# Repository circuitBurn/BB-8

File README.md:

# PCB files and Arduino sketches for FrSky SBUS control of Joe's Drive

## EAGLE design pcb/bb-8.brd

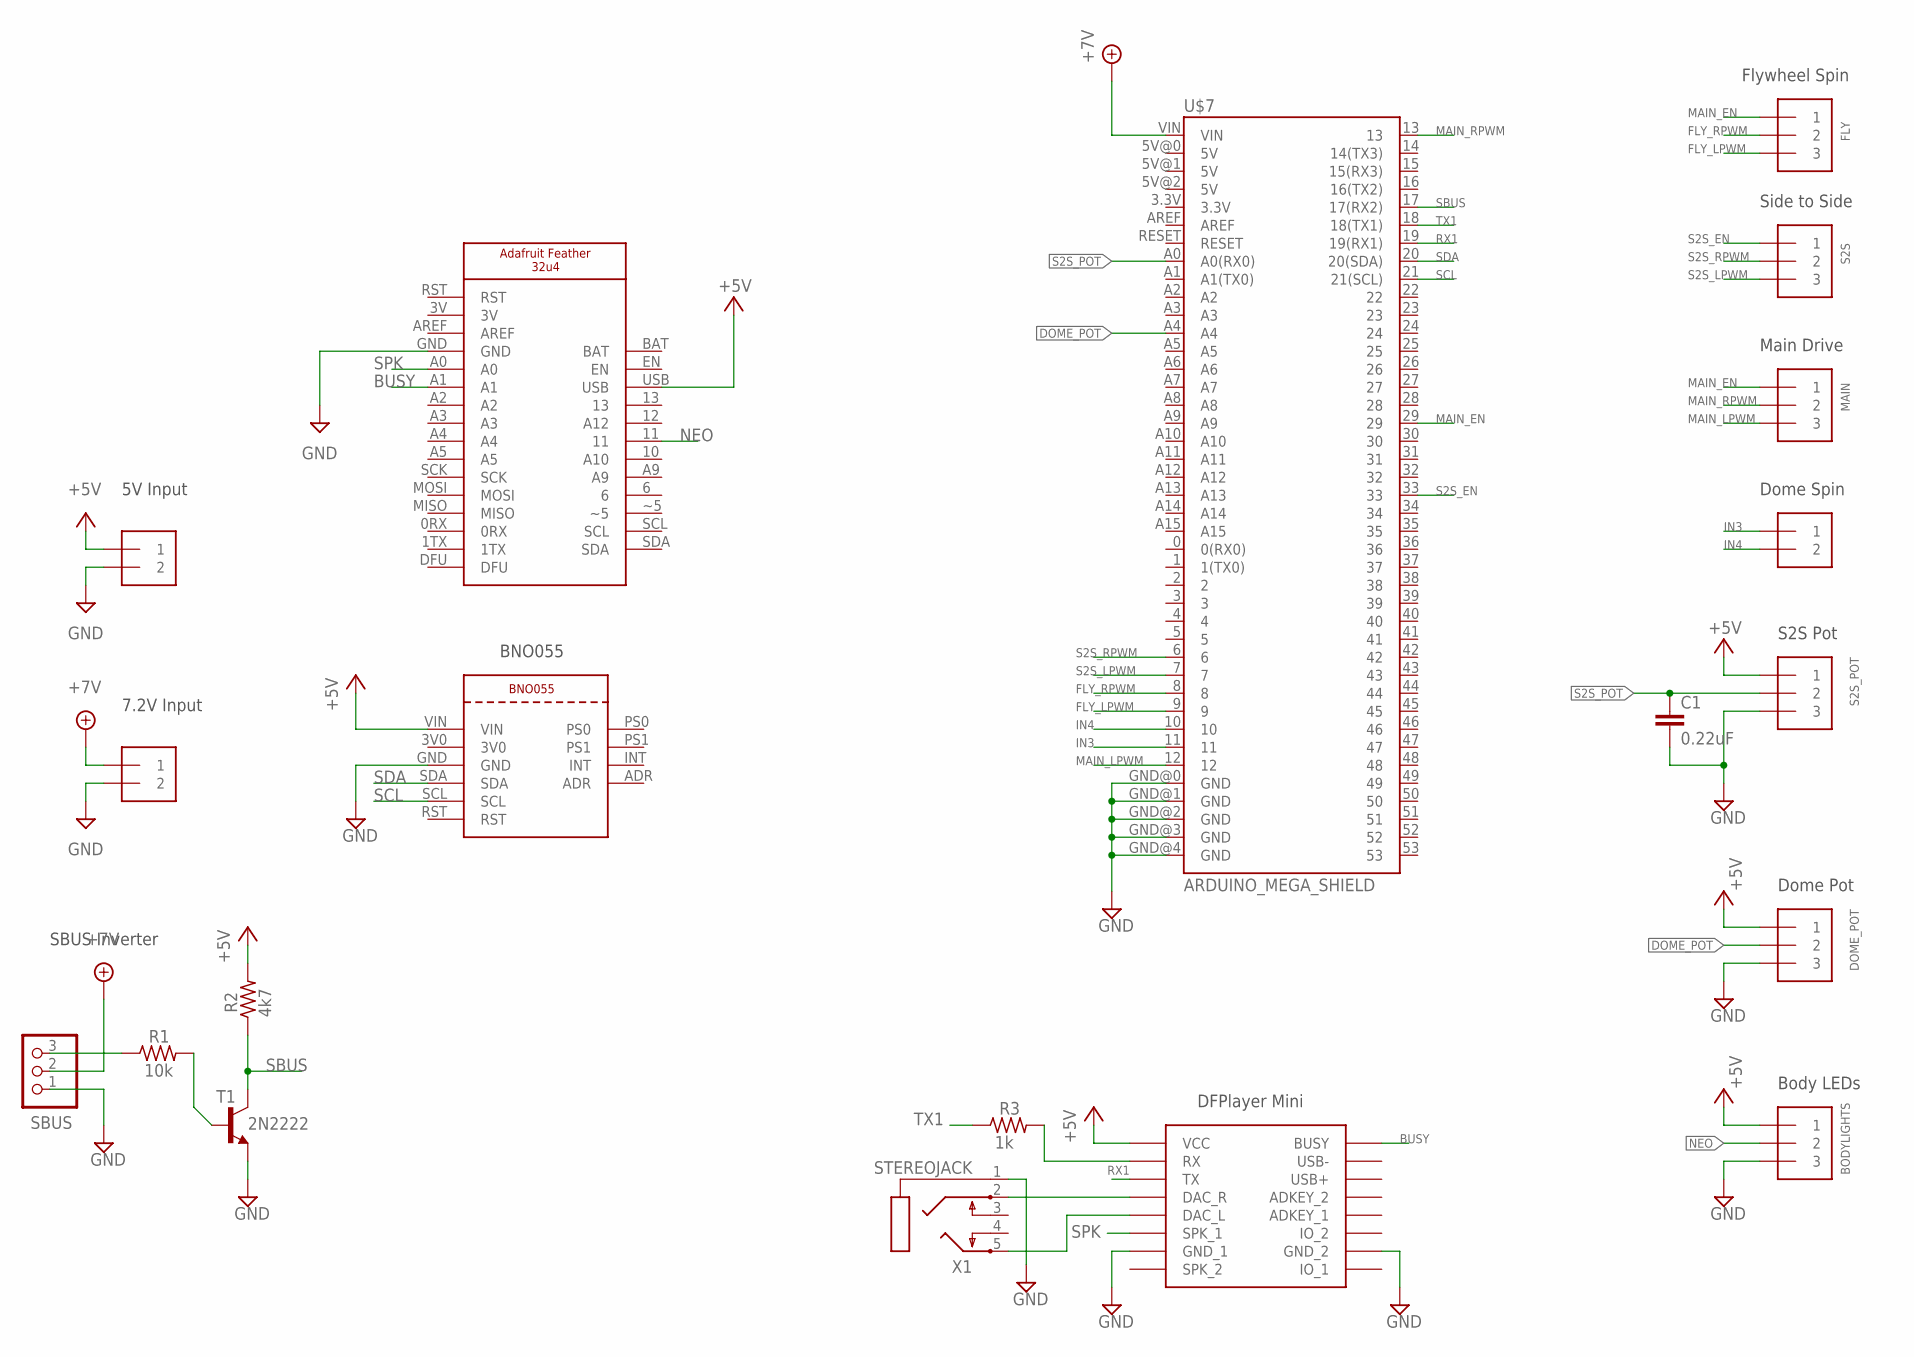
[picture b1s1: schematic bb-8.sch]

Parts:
5V, 7V2: 1X2-3.5MM
BODYLIGHTS: SCREW_TERMINAL_3_PIN
C1: 0.22uF; C050-024X044
DOME: 1X2-3.5MM
DOME_POT: SCREW_TERMINAL_3_PIN
FLY: SCREW_TERMINAL_3_PIN
MAIN: SCREW_TERMINAL_3_PIN
R1: 10k; 0204/7
R2: 4k7; 0204/7
R3: 1k; 0204/7
S2S, S2S_POT: SCREW_TERMINAL_3_PIN
SBUS: PINHD-1X3; 1X03
T1: 2N2222; TO92-EBC-OVAL
U$1: DFPLAYER
U$2: ADAFRUIT_BNO055
U$3: ADAFRUIT_FEATHER_32U4
U$7: ARDUINO_MEGA_SHIELD
X1: STEREOJACK; STX3100

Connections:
+5V: 5V.1, BODYLIGHTS.1, DOME_POT.1, R2.2, S2S_POT.1, U$1.VCC, U$2.VIN, U$3.USB
+7V: 7V2.1, SBUS.2, U$7.VIN
BUSY: U$1.BUSY, U$3.A1
DAC_R: U$1.DAC_R, X1.2
DOME_POT: DOME_POT.2, U$7.A4
FLY_LPWM: FLY.3, U$7.9
FLY_RPWM: FLY.2, U$7.8
GND: 5V.2, 7V2.2, BODYLIGHTS.3, C1.2, DOME_POT.3, S2S_POT.3, SBUS.1, T1.E, U$1.GND_1, U$1.GND_2, U$2.GND, U$3.GND, U$7.GND@0 (GND), U$7.GND@1 (GND), U$7.GND@2 (GND), U$7.GND@3 (GND), U$7.GND@4 (GND), X1.1
IN3: DOME.1, U$7.11
IN4: DOME.2, U$7.10
MAIN_EN: FLY.1, MAIN.1, U$7.29
MAIN_LPWM: MAIN.3, U$7.12
MAIN_RPWM: MAIN.2, U$7.13
unnamed: R1.2, T1.B
unnamed: R3.2, U$1.RX
unnamed: R1.1, SBUS.3
unnamed: U$1.DAC_L, X1.5
NEO: BODYLIGHTS.2, U$3.11
RX1: U$1.TX, U$7.19 (19(RX1))
S2S_EN: S2S.1, U$7.33
S2S_LPWM: S2S.3, U$7.7
S2S_POT: C1.1, S2S_POT.2, U$7.A0 (A0(RX0))
S2S_RPWM: S2S.2, U$7.6
SBUS: R2.1, T1.C, U$7.17 (17(RX2))
SCL: U$2.SCL, U$7.21 (21(SCL))
SDA: U$2.SDA, U$7.20 (20(SDA))
SPK: U$1.SPK1 (SPK_1), U$3.A0
TX1: R3.1, U$7.18 (18(TX1))

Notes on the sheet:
5V Input
7.2V Input
DFPlayer Mini
S2S Pot
Dome Pot
Flywheel Spin
Side to Side
Main Drive
Dome Spin
SBUS Inverter
BNO055
Body LEDs

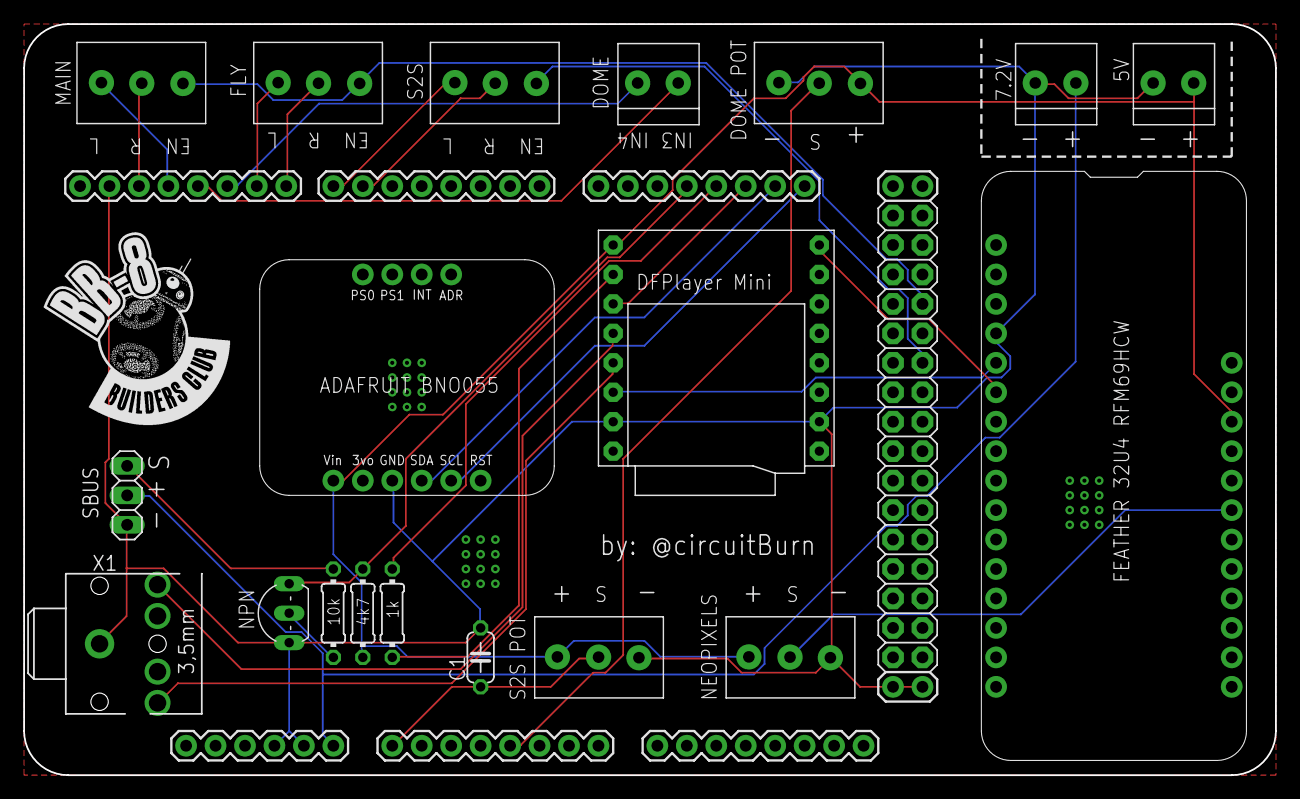
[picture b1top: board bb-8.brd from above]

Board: 2 copper layers, 108.0 x 64.8 mm, 20 parts (0 on the bottom side), 28 nets.

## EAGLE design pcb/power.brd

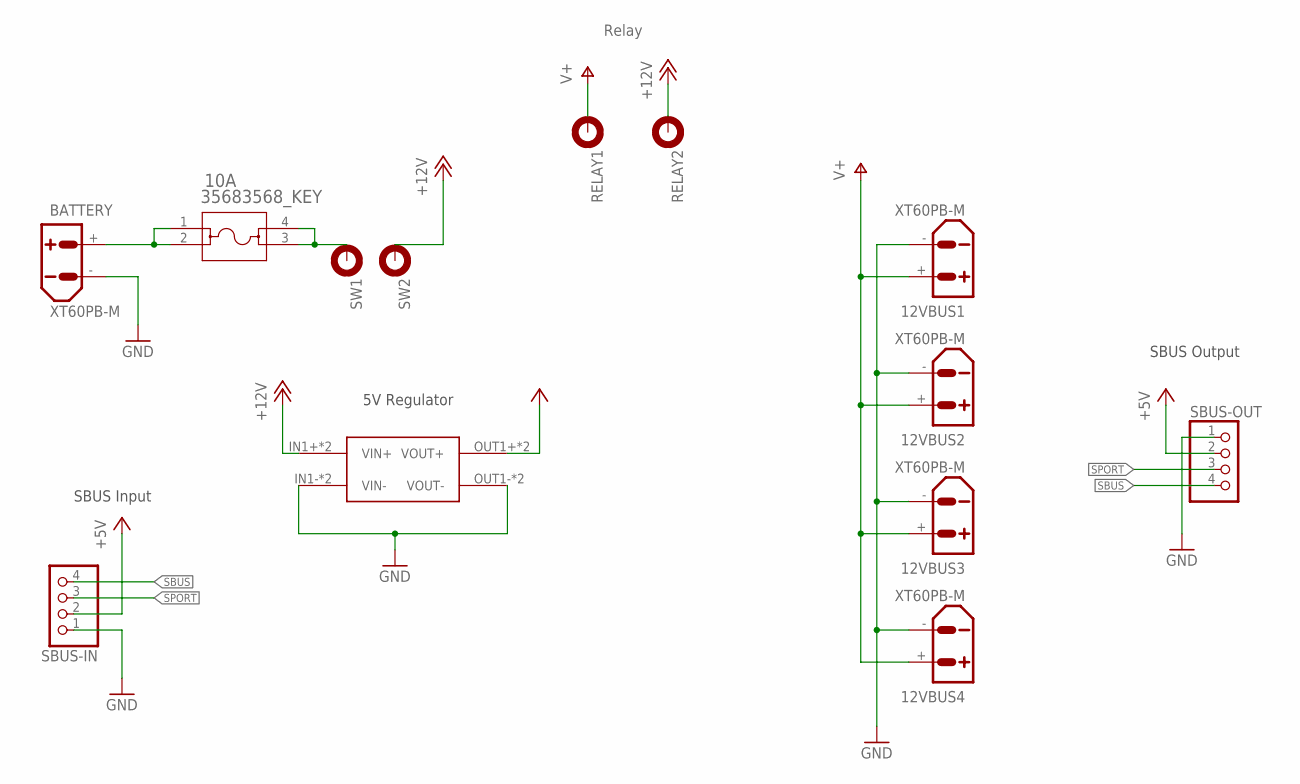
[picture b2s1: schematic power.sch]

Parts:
10A: 35683568_KEY; 3568_KEY
12VBUS1, 12VBUS2, 12VBUS3, 12VBUS4: XT60PB-M
BATTERY: XT60PB-M
RELAY1, RELAY2: MOUNT-PAD-ROUND2.8; 2,8-PAD
SBUS-IN: PINHD-1X4; 1X04
SBUS-OUT: PINHD-1X4; 1X04
SW1, SW2: MOUNT-PAD-ROUND2.8; 2,8-PAD
U$2: MP1584; DC-BRICK

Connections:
+5V: SBUS-IN.2, SBUS-OUT.2, U$2.OUT1+ (VOUT+), U$2.OUT2+ (VOUT+)
+12V: RELAY2.B2,8, SW2.B2,8, U$2.IN1+ (VIN+), U$2.IN2+ (VIN+)
GND: 12VBUS1.-, 12VBUS2.-, 12VBUS3.-, 12VBUS4.-, BATTERY.-, SBUS-IN.1, SBUS-OUT.1, U$2.IN1- (VIN-), U$2.IN2- (VIN-), U$2.OUT1- (VOUT-), U$2.OUT2- (VOUT-)
unnamed: 10A.1, 10A.2, BATTERY.+
unnamed: 10A.3, 10A.4, SW1.B2,8
SBUS: SBUS-IN.4, SBUS-OUT.4
SPORT: SBUS-IN.3, SBUS-OUT.3
V+: 12VBUS1.+, 12VBUS2.+, 12VBUS3.+, 12VBUS4.+, RELAY1.B2,8

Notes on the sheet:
SBUS Output
5V Regulator
SBUS Input
Relay

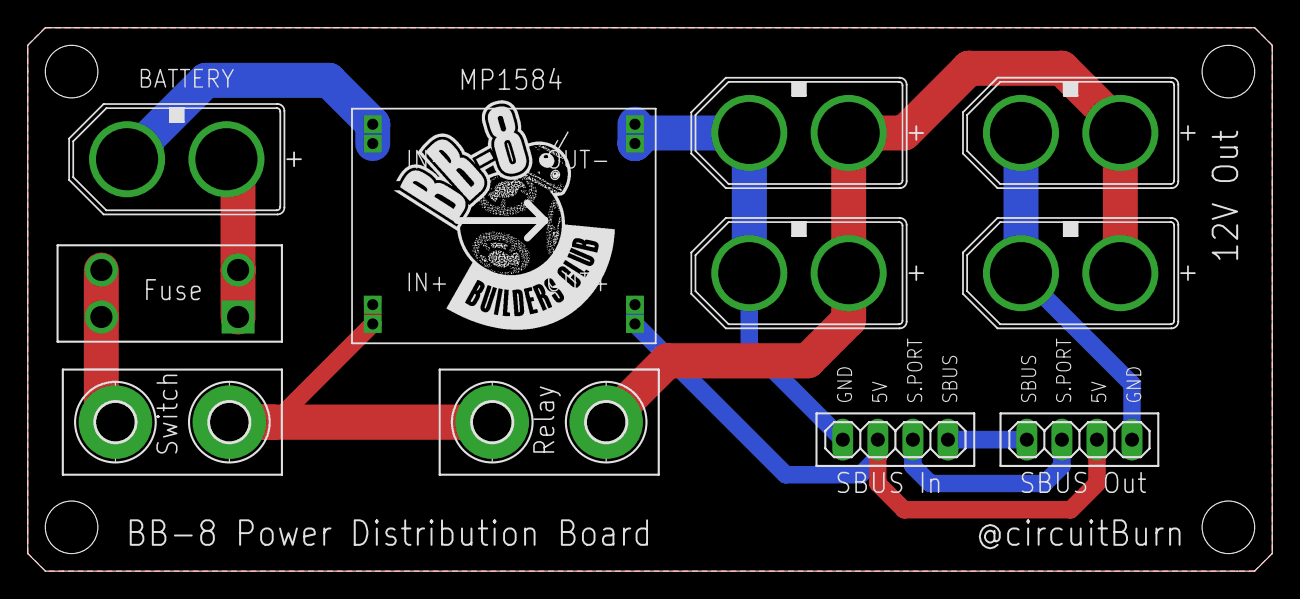
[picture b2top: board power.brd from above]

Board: 2 copper layers, 90.2 x 39.4 mm, 13 parts (0 on the bottom side), 8 nets.

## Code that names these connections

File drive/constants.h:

/*****************************************************************************/
// RC Values
// - These are defined by the limits of your transmitter
/*****************************************************************************/
#define RC_MIN 172
#define RC_MID 992
#define RC_MAX 1811

/*****************************************************************************/
// RC Deadband
// - Set a range of values to be considered "off"
// - Anything in between these values is "off"
/*****************************************************************************/
#define RC_DEADBAND_LOW 962
#define RC_DEADBAND_HIGH 978

/*****************************************************************************/
// RC Channel Mapping
// - The channels are N - 1 where N is the defined channel number on the transmitter
// - Ex: CH1 on Tx is 0 here, CH2 is 1
/*****************************************************************************/
#define CH_DRIVE_MAIN 0
// 1: Channel 2 is directly connected to dome servo
// 2: Channel 3 is directly connected to dome servo 
#define CH_DRIVE_S2S 3
#define CH_FLYWHEEL 4
#define CH_DOME_SPIN 5
// 6: Channel 7 is the RC relay
#define CH_SOUND_TRIGGER 7
#define CH_SOUND_BANK 8
#define CH_DRIVE_EN 9
#define CH_DIRECTION 10
#define CH_ROLL_OFFSET 11
#define CH_FLYWHEEL_EN 12
#define CH_S2S_OFFSET 13
#define CH_RANDOM_SOUND 14

/*****************************************************************************/
// Main drive motor controller
/*****************************************************************************/
#define DRIVE_R_PWM_PIN 13
#define DRIVE_L_PWM_PIN 12
#define DRIVE_EN_PIN 29
#define MAX_DRIVE_SPEED 125 // 0 - 255

/*****************************************************************************/
// Flywheel motor controller
/*****************************************************************************/
#define FLYWHEEL_R_PWM_PIN 8
#define FLYWHEEL_L_PWM_PIN 9

/*****************************************************************************/
// Side to side motor controller
/*****************************************************************************/
#define S2S_R_PWM_PIN 6
#define S2S_L_PWM_PIN 7
#define S2S_EN_PIN 33
#define S2S_POT_PIN A0
#define S2S_MAX_ANGLE 40
#define S2S_EASING 0.9
#define S2S_OFFSET 0 // Negative value here will tilt the drive to the right

/*****************************************************************************/
// Dome servos and spin motor
/*****************************************************************************/
#define DOME_SPIN_A_PIN 10
#define DOME_SPIN_B_PIN 11
#define DOME_POT_PIN A4
#define DOME_SPIN_SPEED 125 // 0 - 255 for spinning completely around
#define DOME_TURN_SPEED 100 // 0 - 255 for looking around
#define DOME_POT_OFFSET 20

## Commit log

2021-07-19 Adding EAGLE PCB schematic and board files
2021-07-31 Initial commit of existing code
2021-09-07 S2S working
2021-09-08 Adding drive feather sketch
2021-09-21 Body Neopixels
2021-09-21 S2S and audio update
2021-09-27 PSI synch
2021-10-07 Big updates
2021-10-13 Fixing dome servo code
2021-10-20 Side to side enhancements
2021-10-20 Update Feather encryption keys
2021-11-05 Moving to 3 axis stick for dome rotation
2021-11-14 Add bodge factor to S2S
2021-12-21 Schematic updates
2022-03-21 A few updates
2022-07-01 Splitting up drive functions into separate files
2022-08-20 Squashed commit of the following:
    commit c327650e5103bb6a6949c6a1538a163dea4dba5a
    Author: Patrick Ryan <pat.m.ryan@gmail.com>
    Date: Sat Aug 20 09:49:49 2022 -0400
    Updates to PCB
    commit 971e034c2edcb3dc5db781baa092387508605f21
    Author: Patrick Ryan <pat.m.ryan@gmail.com>
2022-11-03 Adding quick reverse switch
2023-03-15 Updating sbus library and speed settings
2023-06-17 s2s updates
2023-09-07 Better stabilization
2023-11-05 Updates for horus conversion
2023-11-05 Squashed commit of the following:
    commit f203abea31c9a2bd491b616c386e3c3154b03d5b
    Author: Patrick Ryan <pat.m.ryan@gmail.com>
    Date: Sun Nov 5 11:14:12 2023 -0500
    Updates for horus conversion
2024-01-27 Removing backup files
2024-01-27 Removing unused files
2024-01-27 Adding power board PCB and schematic
2024-01-27 Moving functions into respective files and cleanup
2025-07-21 Code cleanup
2025-07-21 Updates to board
2025-08-09 Setting initial S2S_OFFSET to 0
2025-08-09 Updating PCB
    - Removing I2C lines
    - Fixing PCB power issues

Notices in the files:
parts and their libraries:
BB8: Licensing: Creative Commons ShareAlike 4.0 International - https://creativecommons.org/licenses/by-sa/4.0
COPYRIGHT: Copyright (C) 2023 Ultra Librarian. All rights reserved.
